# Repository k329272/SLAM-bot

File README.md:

# SLAM Bot
---
*Utilizing lidar to control robot via web UI with thetastar navigation*
---
## SLAM
### Simultanious localization and mapping, it finds the location of the robot relative to a map, and also discovers new parts of the map, simultaniously, as the name should suggest.
---
## Thetastar
### I didn't use the star symbol because I don't want to mess up the markdown. Thetastar is a vairiation of a star that uses line of sight (los) checks across the bitmap to see if a node is reachable. Currently, it calculates a route based off of a point given in the web browser
---
## Improvements later on:
- Using arcs for thetastar calculations
- Optimizing for time instead of distance with physics calculations
- Running neural networks on the robot for navigation
- Tracking and following objects
- Implementing 3D lidar or ToF
- More advanced navigation (Routines, avoid other moving objects.
---
## List of parts:
- 1 x Raspberry Pi Zero 2 W
- 2 x DfRobot Micro DC Motor with Encoder-SJ01
- 1 x Printed circuit board
- 1 x Raspberry Pi Header
- 1 x RpLidar A1
- 1 x 9 Volt battery
- 1 x Barrel jack adapter for battery
- 1 x Barrel jack for circuit board
- 1 x 5V regulator (1.5 A)
- 1 x 30mm Fan

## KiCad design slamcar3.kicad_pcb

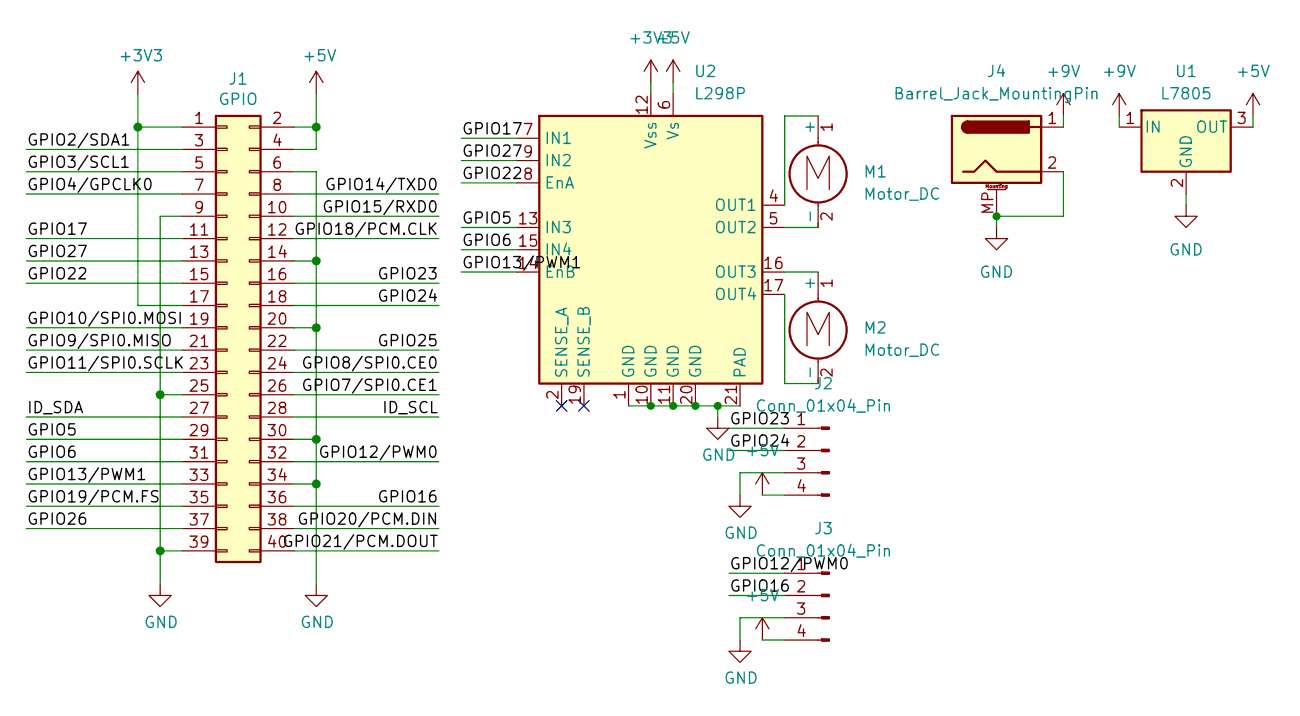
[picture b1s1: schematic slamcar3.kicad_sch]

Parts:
J1: GPIO; PinSocket_2x20_P2.54mm_Vertical
J2, J3: Conn_01x04_Pin; PinHeader_1x04_P2.54mm_Vertical
J4: Barrel_Jack_MountingPin; BarrelJack_Horizontal
M1, M2: Motor_DC; PinHeader_1x02_P2.54mm_Vertical
U1: L7805; TO-252-3_TabPin2
U2: L298P; HSOP-20-1EP_11.0x15.9mm_P1.27mm_SlugDown

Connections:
+3V3: J1.1, J1.17, U2.12 (Vss)
+5V: J1.2, J1.4, J2.4, J3.4, U1.3 (OUT), U2.6 (Vs)
+9V: J4.1, U1.1 (IN)
/GPIO2/SDA1: J1.3
/GPIO3/SCL1: J1.5
/GPIO4/GPCLK0: J1.7
/GPIO5: J1.29, U2.13 (IN3)
/GPIO6: J1.31, U2.15 (IN4)
/GPIO7/SPI0.CE1: J1.26
/GPIO8/SPI0.CE0: J1.24
/GPIO9/SPI0.MISO: J1.21
/GPIO10/SPI0.MOSI: J1.19
/GPIO11/SPI0.SCLK: J1.23
/GPIO12/PWM0: J1.32, J3.1
/GPIO13/PWM1: J1.33, U2.14 (EnB)
/GPIO14/TXD0: J1.8
/GPIO15/RXD0: J1.10
/GPIO16: J1.36, J3.2
/GPIO17: J1.11, U2.7 (IN1)
/GPIO18/PCM.CLK: J1.12
/GPIO19/PCM.FS: J1.35
/GPIO20/PCM.DIN: J1.38
/GPIO21/PCM.DOUT: J1.40
/GPIO22: J1.15, U2.8 (EnA)
/GPIO23: J1.16, J2.1
/GPIO24: J1.18, J2.2
/GPIO25: J1.22
/GPIO26: J1.37
/GPIO27: J1.13, U2.9 (IN2)
/ID_SCL: J1.28
/ID_SDA: J1.27
GND: J1.6, J1.9, J1.14, J1.20, J1.25, J1.30, J1.34, J1.39, J2.3, J3.3, J4.2, J4.MP (MountPin), U1.2 (GND), U2.1 (GND), U2.10 (GND), U2.11 (GND), U2.20 (GND), U2.21 (PAD)
unnamed: M1.1 (+), U2.4 (OUT1)
unnamed: M1.2 (-), U2.5 (OUT2)
unnamed: M2.1 (+), U2.16 (OUT3)
unnamed: M2.2 (-), U2.17 (OUT4)

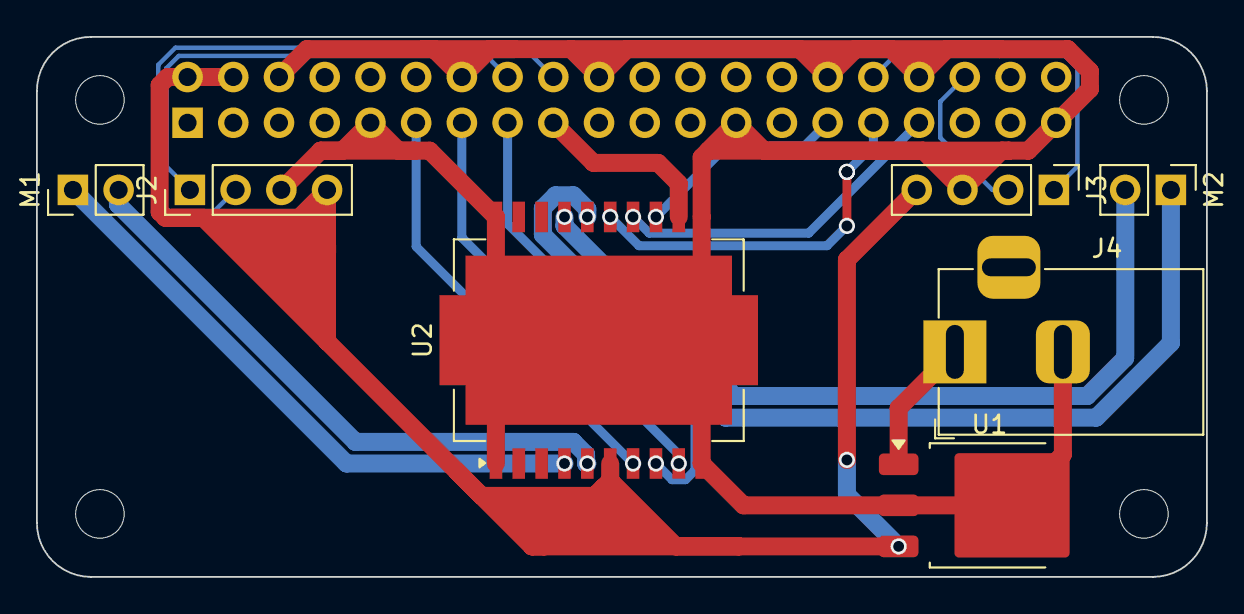
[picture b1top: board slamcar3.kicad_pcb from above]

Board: 2 copper layers, 65.0 x 30.0 mm, 12 parts (1 on the bottom side), 18 nets.

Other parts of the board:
MH1, MH2, MH3, MH4: MountingHole_2.7mm_M2.5

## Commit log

2025-11-29 Move to KiCad folder
2025-11-29 Rename Part Studio 1 - Part 2.3mf to Cad/Part1.3mf
2025-11-29 Rename Part Studio 1 - Part 3.3mf to Cad/Part2.3mf
2025-11-29 Add motor control with PID and encoder support
    Implement L298N motor control with PID velocity control and encoder reading for Raspberry Pi.
2025-11-29 Add LidarDriver class for LIDAR data acquisition
    Implement LidarDriver class for RPLidar interaction
2025-11-29 Add SimpleSLAM implementation with occupancy grid
    This file implements a SimpleSLAM algorithm with an occupancy grid for mapping and localization. It includes utility functions for polar to Cartesian conversion, point transformation, and Bresenham's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
2025-11-29 Add ThetaStarPlanner for path planning
    Implement Theta* path planning algorithm with occupancy grid checks and line of sight validation.
2025-11-29 Add web UI for robot control and visualization
    Flask + SocketIO UI (streams map images and receives goal clicks)
2025-11-29 Add static HTML template for RPLIDAR SLAM UI
2025-11-29 Rename static.html to index.html
2025-11-29 Add main.py for robot control and SLAM integration
2025-11-29 Create setup script for AI project dependencies
    This script installs necessary packages and starts the pigpiod service.
2025-11-29 Create README.md for SLAM Bot project
    Add initial documentation for SLAM Bot project
2025-11-29 Fix markdown formatting in README.md
2025-11-29 Fix typo in README.md
2025-11-29 Add list of parts to README
    Added a list of parts required for the project.
2025-11-29 Add journal entries for November 28 and 29
2025-11-29 Add Top.step file to Cad directory
2025-11-29 Add Bottom.step to Cad directory
2025-11-29 Rename Part Studio 1.step to Cad/Everything.step
2025-11-29 Rename zippedwrl.zip to KiCad/zippedwrl.zip
2025-11-29 Revise JOURNAL.md with detailed entries
    Updated journal entries with detailed tasks for each date.
